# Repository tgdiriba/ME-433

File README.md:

ME-433 Repo
===

+ HW 1 Uploaded

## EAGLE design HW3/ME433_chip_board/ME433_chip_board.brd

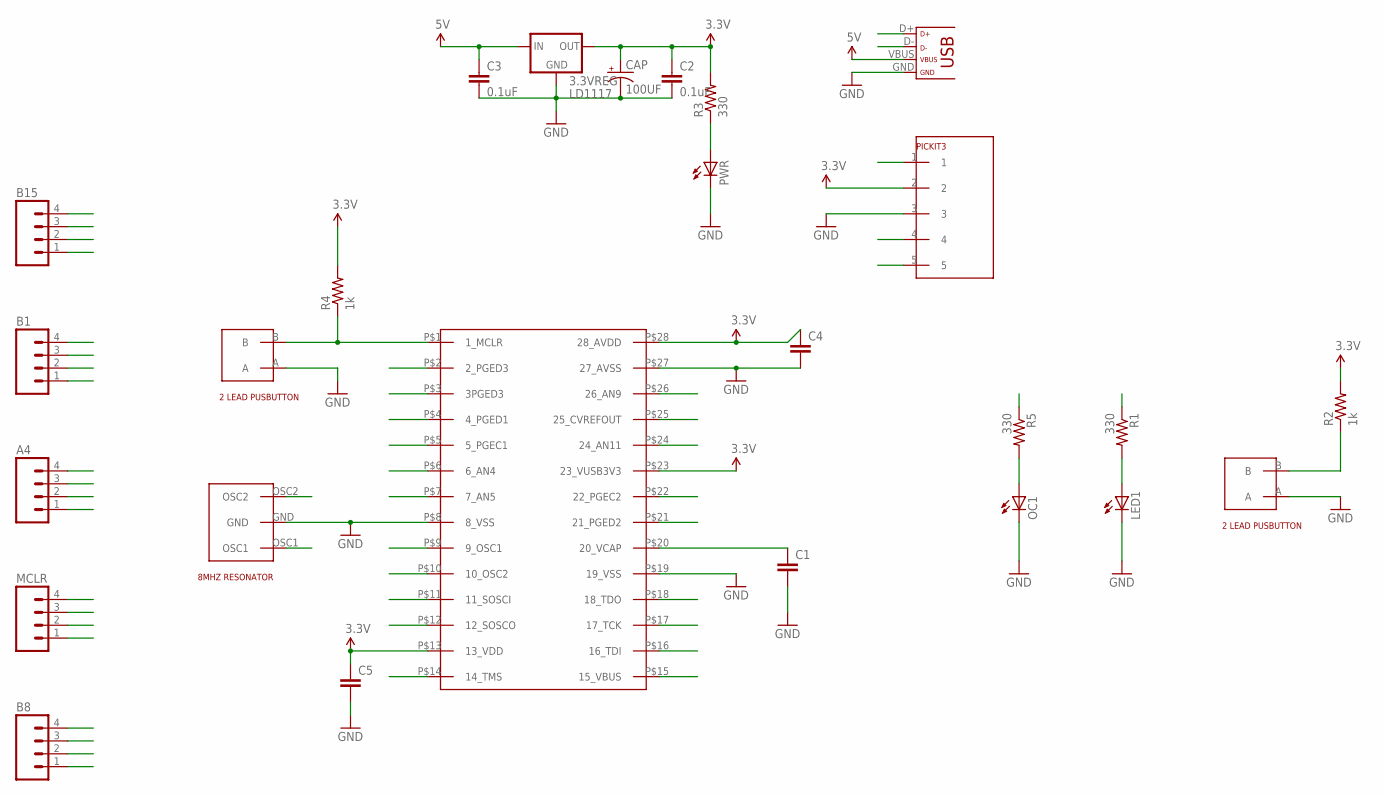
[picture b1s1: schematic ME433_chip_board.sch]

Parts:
3.3VREG: LD1117; TO220
A4: M04PTH; 1X04
B1, B8, B15: M04PTH; 1X04
C1, C4, C5: CAP0603-CAP; 0603-CAP
C2, C3: 0.1uF; 0603-CAP
CAP: 100UF; CAP_POL_D
LED1: TLLR4400; LED3MM
MCLR: M04PTH; 1X04
OC1: TLLR4400; LED3MM
PICKIT3: 1X05_HEADER; 1X05
PWR: TLLY4400; LED3MM
R1, R3, R5: 330; 0603-RES
R2, R4: 1k; 0603-RES
U$1: PIC32MX250F128B
U$3, U$7: 2LEAD_PUSHBUTTON
U$6: 8MHZ_RESONATOR
USB: USB; USB-MINIB

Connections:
3.3V: 3.3VREG.2 (OUT), A4.1, C2.1, C4.1, C5.1, CAP.1 (+), PICKIT3.2, R2.2, R3.2, R4.2, U$1.P$13 (13_VDD), U$1.P$23 (23_VUSB3V3), U$1.P$28 (28_AVDD)
5V: 3.3VREG.3 (IN), B8.1, C3.1, U$1.P$15 (15_VBUS), USB.VBUS
A0: B15.3, U$1.P$2 (2_PGED3)
A1: B15.2, U$1.P$3 (3PGED3)
A4: A4.4, U$1.P$12 (12_SOSCO)
B0: B15.1, PICKIT3.4, U$1.P$4 (4_PGED1)
B1: B1.4, PICKIT3.5, U$1.P$5 (5_PGEC1)
B2: B1.3, U$1.P$6 (6_AN4)
B3: B1.2, U$1.P$7 (7_AN5)
B4: B1.1, U$1.P$11 (11_SOSCI)
B5: A4.3, U$1.P$14 (14_TMS)
B7: B8.3, R1.1, U$1.P$16 (16_TDI)
B8: B8.4, U$1.P$17 (17_TCK)
B9: MCLR.1, U$1.P$18 (18_TDO)
B13: MCLR.2, R2.1, U$1.P$24 (24_AN11), U$7.B
B14: MCLR.3, U$1.P$25 (25_CVREFOUT)
B15: MCLR.4, R5.1, U$1.P$26 (26_AN9)
D+: U$1.P$21 (21_PGED2), USB.D+
D-: U$1.P$22 (22_PGEC2), USB.D-
GND: 3.3VREG.1 (GND), A4.2, B8.2, C1.2, C2.2, C3.2, C4.2, C5.2, CAP.2 (-), LED1.K (C), OC1.K (C), PICKIT3.3, PWR.K (C), U$1.P$8 (8_VSS), U$1.P$19 (19_VSS), U$1.P$27 (27_AVSS), U$3.A, U$6.GND, U$7.A, USB.GND
MCLR: B15.4, PICKIT3.1, R4.1, U$1.P$1 (1_MCLR), U$3.B
unnamed: LED1.A, R1.2
unnamed: OC1.A, R5.2
unnamed: PWR.A, R3.1
unnamed: C1.1, U$1.P$20 (20_VCAP)
OSC1: U$1.P$9 (9_OSC1), U$6.OSC1
OSC2: U$1.P$10 (10_OSC2), U$6.OSC2

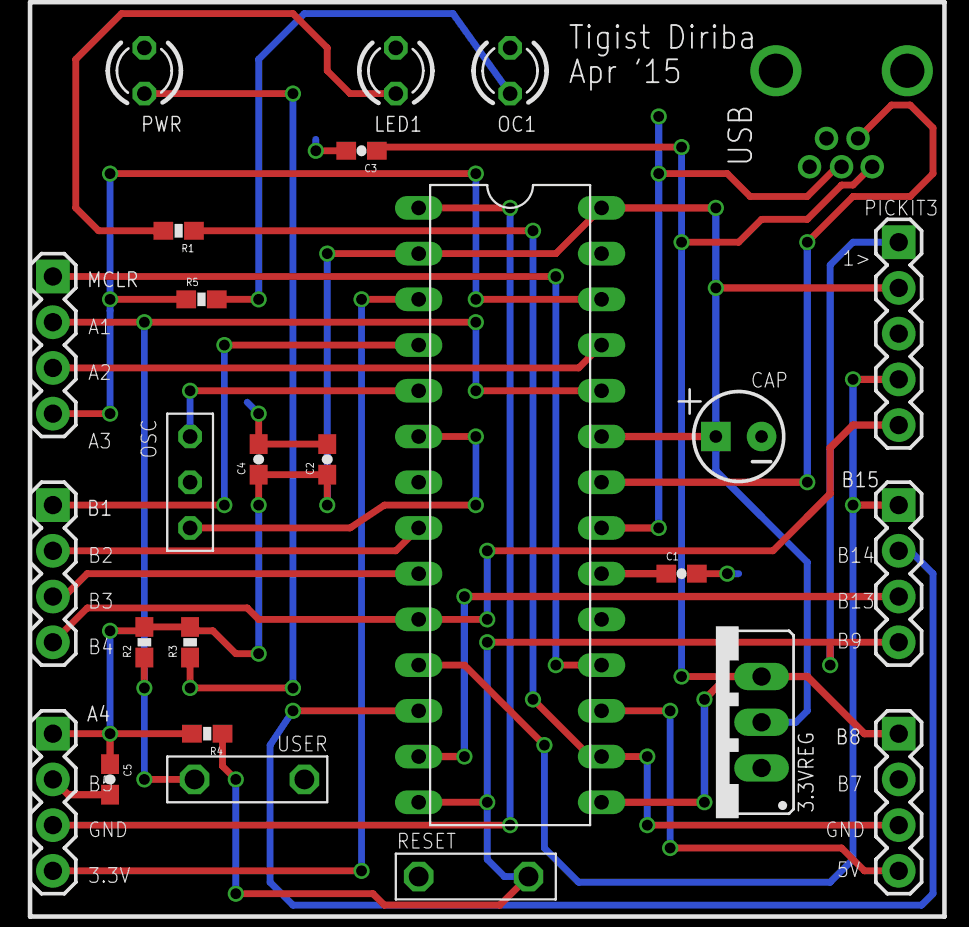
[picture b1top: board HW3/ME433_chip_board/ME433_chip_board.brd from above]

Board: 2 copper layers, 26 parts (0 on the bottom side), 27 nets.

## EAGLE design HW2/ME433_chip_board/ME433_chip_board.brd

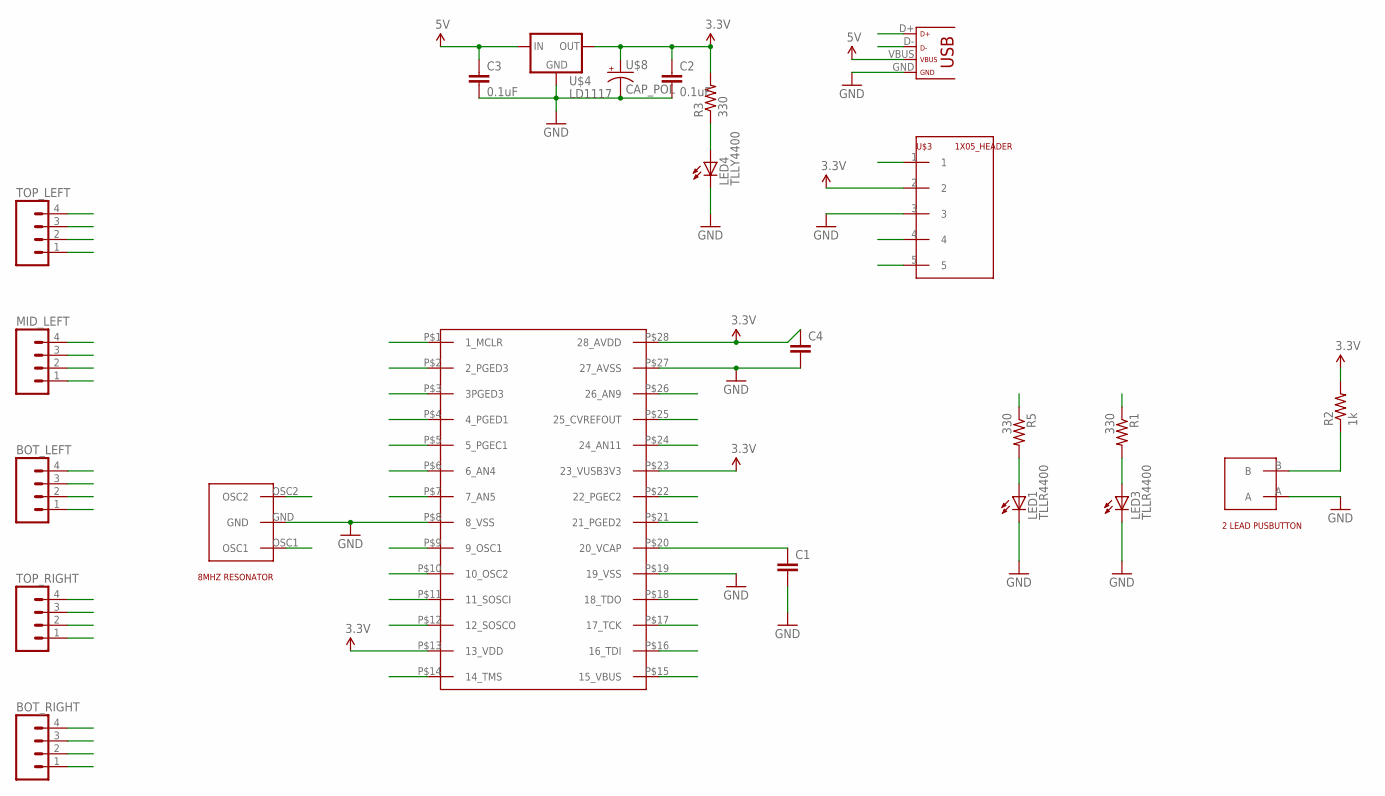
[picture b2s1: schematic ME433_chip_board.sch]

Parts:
BOT_LEFT: M04PTH; 1X04
BOT_RIGHT: M04PTH; 1X04
C1, C4: CAP0603-CAP; 0603-CAP
C2, C3: 0.1uF; 0603-CAP
LED1, LED3: TLLR4400; LED3MM
LED4: TLLY4400; LED3MM
MID_LEFT: M04PTH; 1X04
R1, R3, R5: 330; 0603-RES
R2: 1k; 0603-RES
TOP_LEFT: M04PTH; 1X04
TOP_RIGHT: M04PTH; 1X04
U$1: PIC32MX250F128B
U$2: USB; USB-MINIB
U$3: 1X05_HEADER; 1X05
U$4: LD1117; TO220
U$6: 8MHZ_RESONATOR
U$7: 2LEAD_PUSHBUTTON
U$8: CAP_POL; CAP_POL_D

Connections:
3.3V: BOT_LEFT.1, C2.1, C4.1, R2.2, R3.2, U$1.P$13 (13_VDD), U$1.P$23 (23_VUSB3V3), U$1.P$28 (28_AVDD), U$3.2, U$4.2 (OUT), U$8.1 (+)
5V: BOT_RIGHT.1, C3.1, U$1.P$15 (15_VBUS), U$2.VBUS, U$4.3 (IN)
A0: TOP_LEFT.3, U$1.P$2 (2_PGED3)
A1: TOP_LEFT.2, U$1.P$3 (3PGED3)
A4: BOT_LEFT.4, U$1.P$12 (12_SOSCO)
B0: TOP_LEFT.1, U$1.P$4 (4_PGED1), U$3.4
B1: MID_LEFT.4, U$1.P$5 (5_PGEC1), U$3.5
B2: MID_LEFT.3, U$1.P$6 (6_AN4)
B3: MID_LEFT.2, U$1.P$7 (7_AN5)
B4: MID_LEFT.1, U$1.P$11 (11_SOSCI)
B5: BOT_LEFT.3, U$1.P$14 (14_TMS)
B7: BOT_RIGHT.3, R1.1, U$1.P$16 (16_TDI)
B8: BOT_RIGHT.4, U$1.P$17 (17_TCK)
B9: TOP_RIGHT.1, U$1.P$18 (18_TDO)
B13: R2.1, TOP_RIGHT.2, U$1.P$24 (24_AN11), U$7.B
B14: TOP_RIGHT.3, U$1.P$25 (25_CVREFOUT)
B15: R5.1, TOP_RIGHT.4, U$1.P$26 (26_AN9)
D+: U$1.P$21 (21_PGED2), U$2.D+
D-: U$1.P$22 (22_PGEC2), U$2.D-
GND: BOT_LEFT.2, BOT_RIGHT.2, C1.2, C2.2, C3.2, C4.2, LED1.K (C), LED3.K (C), LED4.K (C), U$1.P$8 (8_VSS), U$1.P$19 (19_VSS), U$1.P$27 (27_AVSS), U$2.GND, U$3.3, U$4.1 (GND), U$6.GND, U$7.A, U$8.2 (-)
MCLR: TOP_LEFT.4, U$1.P$1 (1_MCLR), U$3.1
unnamed: LED3.A, R1.2
unnamed: LED1.A, R5.2
unnamed: LED4.A, R3.1
unnamed: C1.1, U$1.P$20 (20_VCAP)
OSC1: U$1.P$9 (9_OSC1), U$6.OSC1
OSC2: U$1.P$10 (10_OSC2), U$6.OSC2

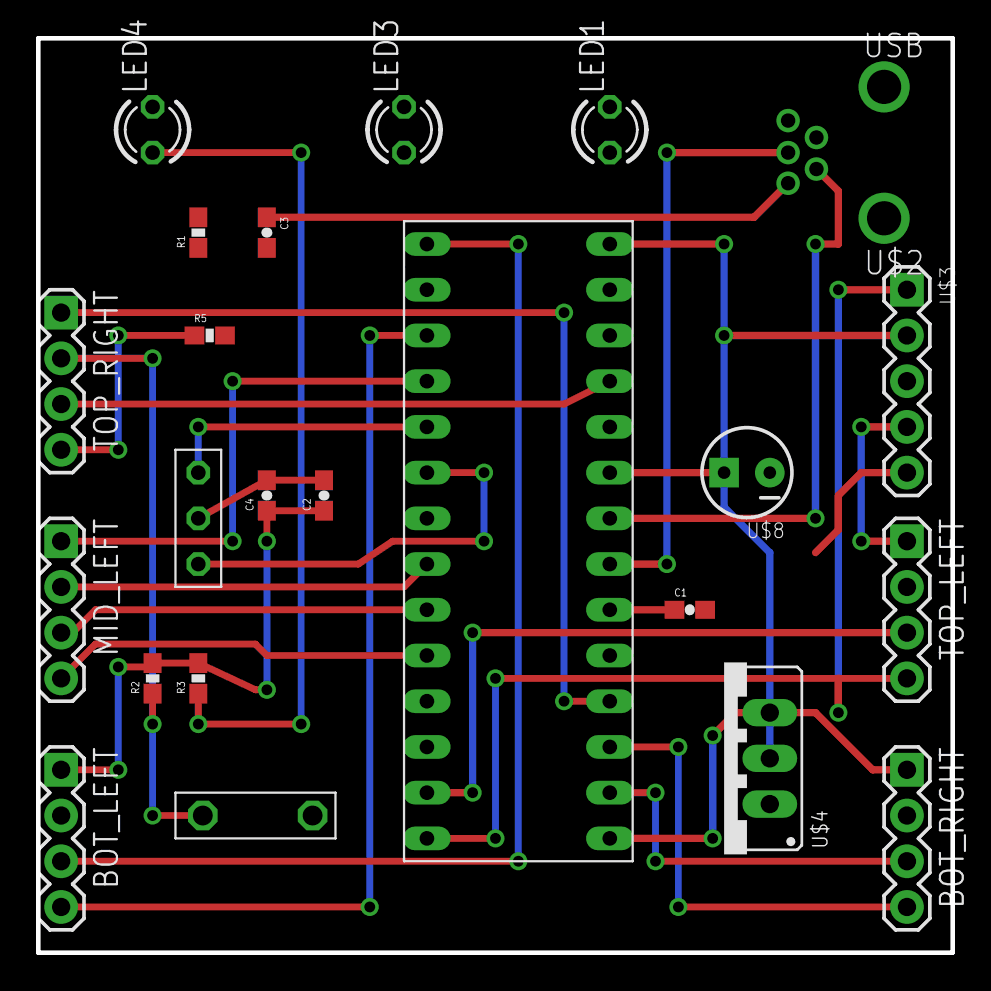
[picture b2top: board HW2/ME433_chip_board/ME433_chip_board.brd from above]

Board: 2 copper layers, 50.8 x 50.8 mm, 23 parts (0 on the bottom side), 27 nets.

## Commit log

2015-04-01 First hw uploaded
2015-04-02 added schematic
2015-04-02 updated schematic
2015-04-02 Removed some things
2015-04-02 Changed resistor in schematic
2015-04-07 Added library with schematic and board
2015-04-09 Added updated schematic and board -- generated gerbers
2015-04-09 Fixed missing capacitor
2015-04-09 starting hw4
2015-04-13 First set of code
2015-04-13 Added more drawing functions
2015-04-14 Working version
2015-04-15 minor bug fix
2015-04-16 hw5 added
2015-04-16 added datasheet
2015-04-22 blinking led using harmony
2015-04-22 added hid mouse
2015-04-22 moved hid mouse
2015-04-22 added display code to hid mouse
2015-05-12 Adding homework 8
2015-06-10 Added all homeworks
2015-06-10 Testing renaming of folder
2015-06-10 Updated 16
2015-06-10 Zipped content in 16 to avoid issues with git submodules

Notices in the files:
parts and their libraries:
SparkFun-Connectors: Licensing: Creative Commons ShareAlike 4.0 International - https://creativecommons.org/licenses/by-sa/4.0
